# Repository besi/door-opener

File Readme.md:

Door Opener
===========

Remotely open the door

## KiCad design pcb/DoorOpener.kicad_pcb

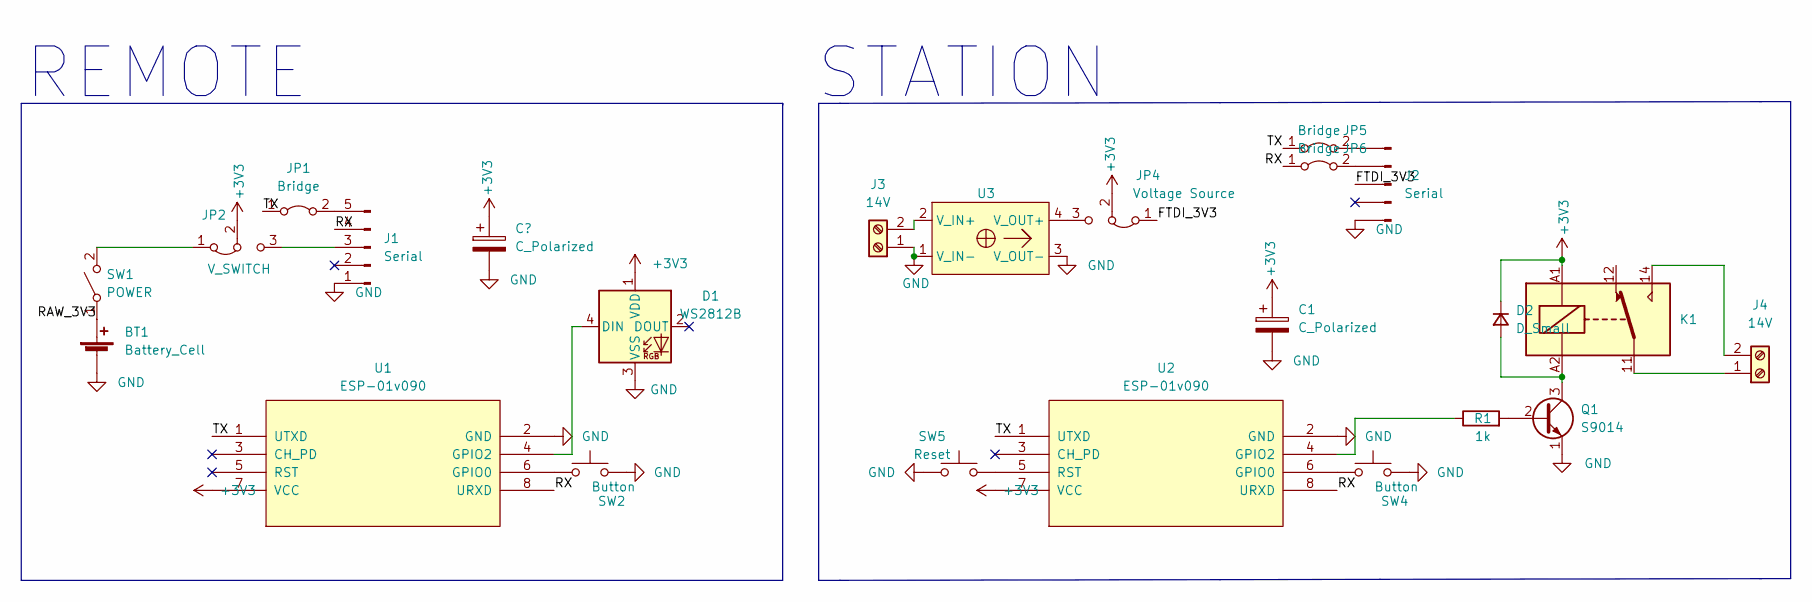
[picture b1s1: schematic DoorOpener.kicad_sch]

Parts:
BT1: Battery_Cell; BatteryHolder_Keystone_2479_3xAAA
C1: C_Polarized; CP_Radial_D5.0mm_P2.50mm
D1: WS2812B; LED_D5.0mm-4_RGB_Wide_Pins
D2: D_Small; D_A-405_P7.62mm_Horizontal
J1, J2: Serial; PinHeader_1x05_P2.54mm_Horizontal
J3, J4: 14V; TerminalBlock_Phoenix_PT-1,5-2-3.5-H_1x02_P3.50mm_Horizontal
JP1, JP6: Bridge; R_Axial_DIN0204_L3.6mm_D1.6mm_P5.08mm_Horizontal
JP2: V_SWITCH; PinHeader_1x03_P2.54mm_Vertical
JP4: Voltage Source; PinHeader_1x03_P2.54mm_Vertical
JP5: Bridge; R_Axial_DIN0204_L3.6mm_D1.6mm_P7.62mm_Horizontal
K1: FINDER-36.11; Relay_SPDT_Finder_36.11
Q1: S9014; PinHeader_1x03_P2.54mm_Vertical
R1: 1k; R_Axial_DIN0204_L3.6mm_D1.6mm_P7.62mm_Horizontal
SW1: POWER; SW_SPDT_CK-JS102011SAQN
SW2, SW4: Button; SW_PUSH_6mm_H4.3mm
SW5: Reset; SW_PUSH_6mm_H4.3mm
U1, U2: ESP-01v090; ESP-01
U3: dcdc

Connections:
+3V3: C1.1, D1.1 (VDD), D2.1 (K), JP2.2 (C), JP4.2 (C), K1.A1, U1.7 (VCC), U2.7 (VCC); also elsewhere on the board
/FTDI_3V3: J2.3, JP4.1 (A)
/RAW_3V3: BT1.1 (+), SW1.1 (A)
/RX: J1.4, JP6.1 (A), U1.8 (URXD), U2.8 (URXD)
/TX: JP1.1 (A), JP5.1 (A), U1.1 (UTXD), U2.1 (UTXD)
GND: BT1.2 (-), C1.2, D1.3 (VSS), J1.1, J2.1, J3.1, Q1.1 (E), SW2.2, SW4.2, SW5.2, U1.2 (GND), U2.2 (GND), U3.1 (V_IN-), U3.3 (V_OUT-); also elsewhere on the board
unnamed: D1.4 (DIN), U1.4 (GPIO2)
unnamed: D2.2 (A), K1.A2, Q1.3 (C)
unnamed: J1.3, JP2.3 (B)
unnamed: J1.5, JP1.2 (B)
unnamed: J2.4, JP6.2 (B)
unnamed: J2.5, JP5.2 (B)
unnamed: J3.2, U3.2 (V_IN+)
unnamed: J4.1, K1.11
unnamed: J4.2, K1.14
unnamed: JP4.3 (B), U3.4 (V_OUT+)
unnamed: Q1.2 (B), R1.2
unnamed: R1.1, U2.4 (GPIO2)
unnamed: JP2.1 (A), SW1.2 (B)
unnamed: SW2.1, U1.6 (GPIO0)
unnamed: SW4.1, U2.6 (GPIO0)
unnamed: SW5.1, U2.5 (RST)

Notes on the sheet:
STATION
REMOTE

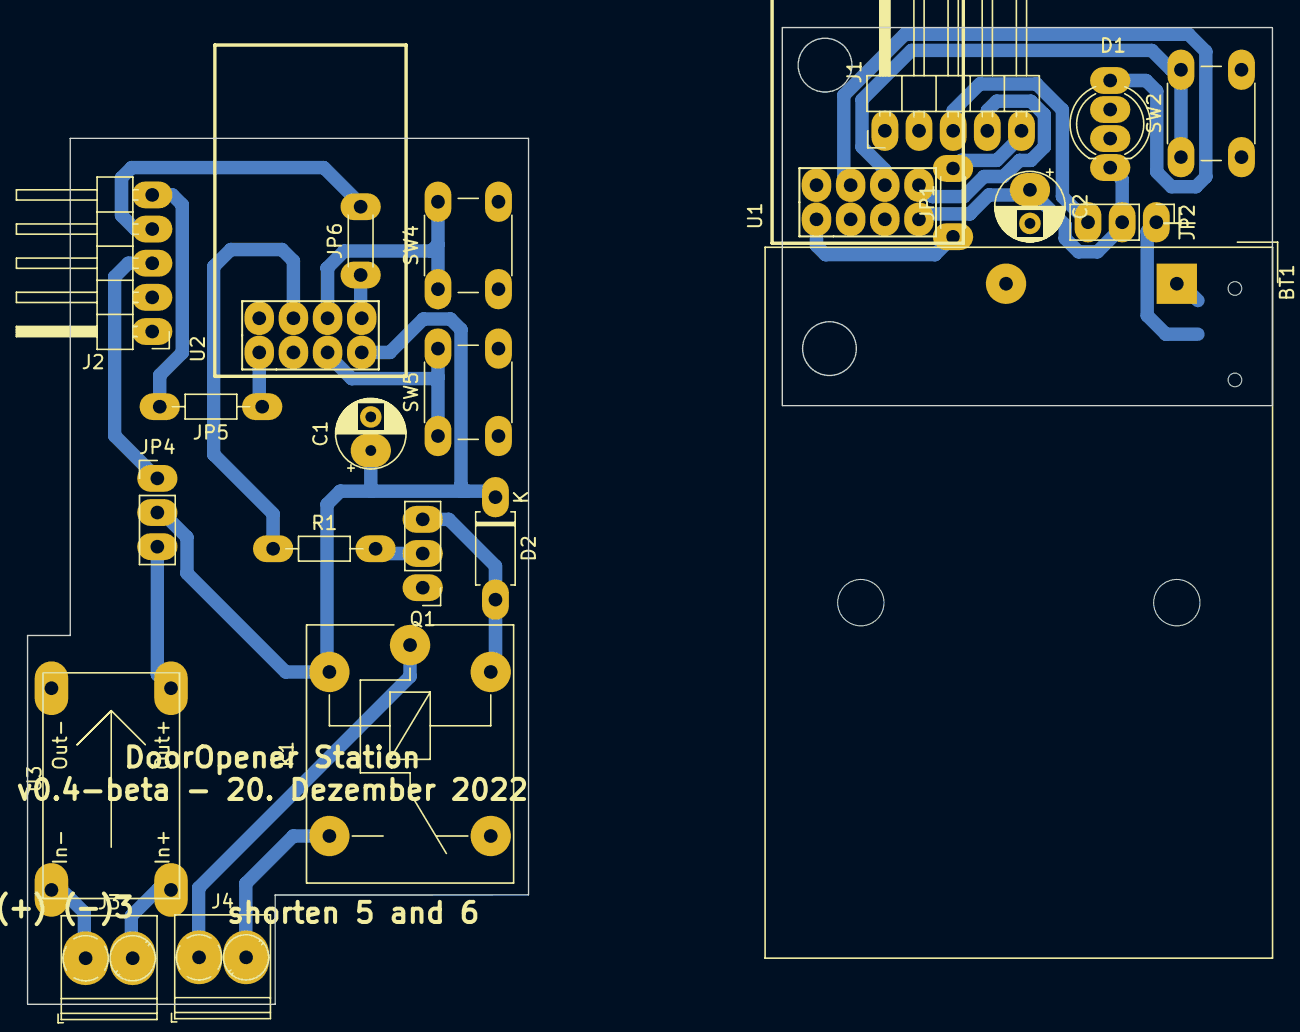
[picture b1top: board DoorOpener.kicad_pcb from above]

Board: 2 copper layers, 92.6 x 72.6 mm, 24 parts (1 on the bottom side), 22 nets.

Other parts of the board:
C2: C_Polarized; CP_Radial_D5.0mm_P2.50mm

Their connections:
+3V3: C2.1; also elsewhere on the board
GND: C2.2; also elsewhere on the board

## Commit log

2022-11-25 Add submodules and initial pcb
2022-11-25 Add 3d model of the switch
2022-11-25 Add mounting holes
2022-11-27 Prepare for milling the pcb
2022-11-29 Add TX RX Connector
2022-11-29 Add rendering
2022-11-29 New rendering
2022-12-03 Version 0.2
2022-12-03 Minor adjustments
2022-12-03 Make the pads as big as possible
2022-12-03 Add FTDI-compatible socket and an option to power from USB
2022-12-04 PCB: Add station module
2022-12-05 Add enclosure dimensions in DWG layer
2022-12-05 Update PCB with the housing constraints
2022-12-07 Update terminal socket footprint and some minor changes
2022-12-07 Update esp8266 kicad library model
2022-12-07 Untrack dcdc module becaus it’s a submodule
2022-12-07 Add relais and dcdc module
2022-12-08 Swap VCC and Signal pin
2022-12-08 Update relais_module
2022-12-11 Fix wrong polarity of the dcdc module and replace the relais circuit
2022-12-15 Label the transistor
2022-12-15 Prepare for 0.3v plot
2022-12-20 Add polarised capacitors for improved stability
    Also add a three way switch for the remote so that the jumper does not get lost and to decouple the battery when FTDI is used.
2025-12-11 Ignore Fab folder
